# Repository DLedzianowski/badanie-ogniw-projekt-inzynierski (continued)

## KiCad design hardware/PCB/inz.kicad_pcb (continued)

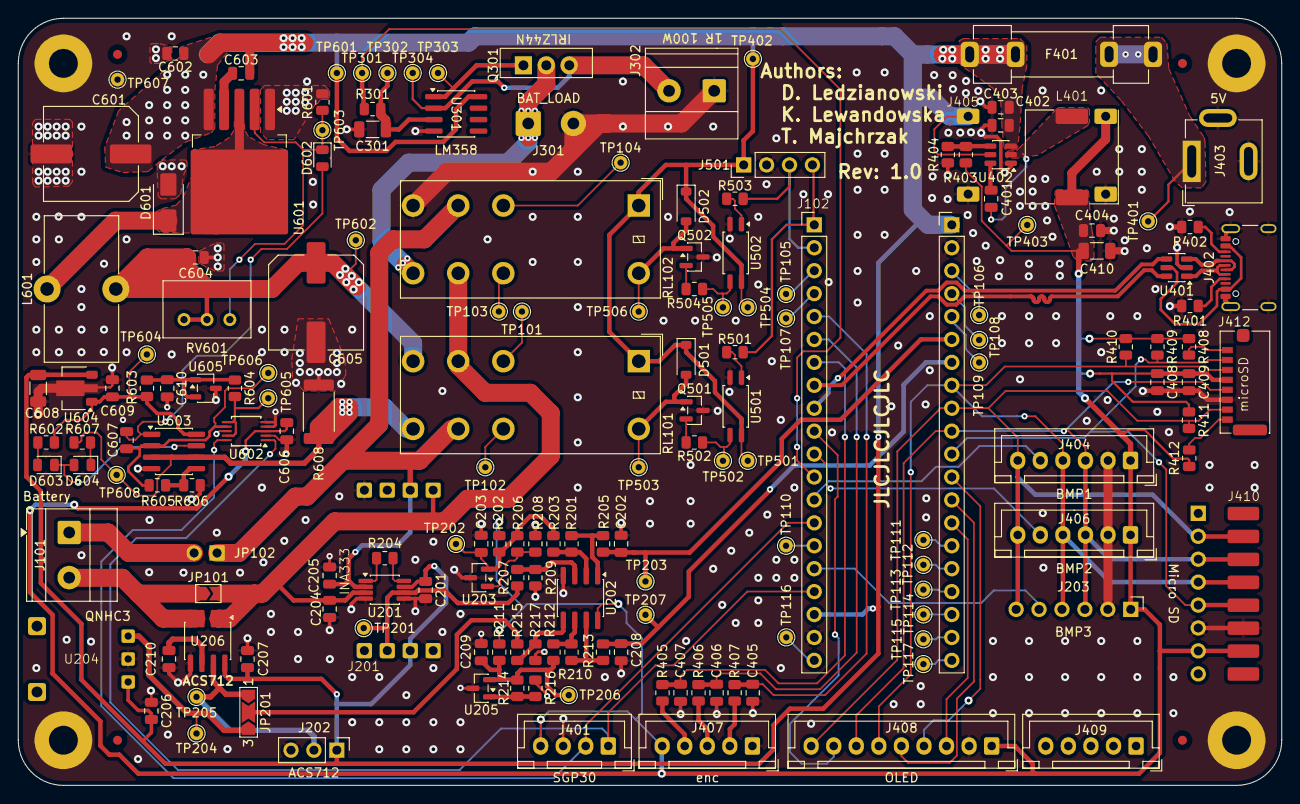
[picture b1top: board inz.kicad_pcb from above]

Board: 2 copper layers, 140.0 x 85.0 mm, 180 parts (0 on the bottom side), 104 nets.

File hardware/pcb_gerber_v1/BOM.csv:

Comment,Designator,Footprint,LCSC part number ,Qty,MFR Part,Manufacturer
100n,"C201,C202,C204,C205,C206,C207,C208,C401,C405,C406,C407,C408",Capacitor_SMD:C_0805_2012Metric,C28233,12," CL21B104KCFNNNE,CL21B104KCFNNNE",Samsung Electro-Mechanics
1u,"C203,C209,C409,C602,C603,C604,C606,C607,C609,C610",Capacitor_SMD:C_0805_2012Metric,C28323,10,CL21B105KBFNNNE,Samsung Electro-Mechanics
1n,C210,Capacitor_SMD:C_0805_2012Metric,C46653,1,CL21B102KBCNNNC,Samsung Electro-Mechanics
10u,"C301,C410,C608",Capacitor_SMD:C_1206_3216Metric,C1849,3,CL31A106KOHNNNE ,Samsung Electro-Mechanics 
2.2u,C402,Capacitor_SMD:C_0805_2012Metric,C377773,1,CL21A225KBQNNNE,Samsung Electro-Mechanics
100n,"C403,C404",Capacitor_SMD:C_0805_2012Metric,C1711,2,CL21B104KBCNNNC,Samsung Electro-Mechanics
470u,"C601,C605",Capacitor_SMD:C_Elec_10x10.2,C3351,2,RVT1E471M1010,Honor Elec
1N4148W,"D501,D502",Diode_SMD:D_SOD-123,C81598,2,1N4148W,ST(Semtech)
MBRD1045,D601,Diode_SMD:D_SMA,C22452,1,C22452,MDD(Microdiode Semiconductor)
Red,D602,LED_SMD:LED_0805_2012Metric,C84256,1,NCD0805R1,Foshan NationStar Optoelectronics
Yellow,D603,LED_SMD:LED_0805_2012Metric,C2296,1,KT-0805Y,Hubei KENTO Elec
Green,D604,LED_SMD:LED_0805_2012Metric,C2297,1,KT-0805G,Hubei KENTO Elec
STM32blackpill,J102,Package_DIP:DIP-40_W15.24mm,C2332,1,ICSockets-40P,BOOMELE(Boom Precision Elec)
"BMP1,BMP2","J404,J406",Connector_JST:JST_XH_B6B-XH-A_1x06_P2.50mm_Vertical,C144397,2,B6B-XH-A(LF)(SN),JST
SGP30,J401,Connector_JST:JST_XH_B4B-XH-A_1x04_P2.50mm_Vertical,C144395,1,B4B-XH-A(LF)(SN),JST
USBC,J402,footprints:USB_C_16P,C47817612,1,TYPE-C-31-M-48,Korean Hroparts Elec
5V,J403,Connector_BarrelJack:BarrelJack_GCT_DCJ200-10-A_Horizontal,C5155559,1,DC-005H-D020,G-Switch
enc,J407,Connector_JST:JST_XH_B5B-XH-A_1x05_P2.50mm_Vertical,C157991,1,B5B-XH-A(LF)(SN),JST
OLED,J408,Connector_JST:JST_XH_B9B-XH-A_1x09_P2.50mm_Vertical,C157966,1,B9B-XH-A(LF)(SN) ,JST
Micro_SD_Card,J412,footprints:microSD,C498185,1,TF-021B-H265,SOFNG
2.2uH,L401,"footprints:SMD,10.4x10.3mm",C10164 ,1,SXN(Shun Xiang Nuo Elec),SMDRH105R-2R2NT 
47u,L601,Inductor_THT:L_Toroid_Vertical_L16.0mm_W8.0mm_P7.62mm,C18213949,1,XR050125TS470MVL8,XR
IRLZ44N,Q301,Package_TO_SOT_THT:TO-220-3_Vertical,C38774,1,IRLZ44NPBF,Infineon Technologies
NPN,"Q501,Q502",Package_TO_SOT_SMD:SOT-23,C20526,2,MMBT3904(RANGE:100-300),"Jiangsu Changjing Electronics Technology Co., Ltd."
6.2k,"R201,R209",Resistor_SMD:R_0805_2012Metric,C17767,2,0805W8F6201T5E,UNI-ROYAL(Uniroyal Elec)
10k,"R202,R206,R208,R211,R216,R408,R409,R410,R411,R412,R606",Resistor_SMD:R_0805_2012Metric,C17414,11,0805W8F1002T5E,UNI-ROYAL(Uniroyal Elec)
3.9k,"R203,R207",Resistor_SMD:R_0805_2012Metric,C17614,2,0805W8F3901T5E,UNI-ROYAL(Uniroyal Elec)
4.7k,"R205,R212,R213,R215",Resistor_SMD:R_0805_2012Metric,C17673,4,0805W8F4701T5E,UNI-ROYAL(Uniroyal Elec)
8.2k,"R210,R217",Resistor_SMD:R_0805_2012Metric,C17828 ,2,0805W8F8201T5E,UNI-ROYAL(Uniroyal Elec)
2.2k,R214,Resistor_SMD:R_0805_2012Metric,C17520 ,1,0805W8F2201T5E,UNI-ROYAL(Uniroyal Elec)
1k,"R301,R602,R607",Resistor_SMD:R_0805_2012Metric,C17513,3,0805W8F1001T5E,UNI-ROYAL(Uniroyal Elec)
5.1k,"R401,R402,R405,R406,R407",Resistor_SMD:R_0805_2012Metric,C27834,5,0805W8F5101T5E ,UNI-ROYAL(Uniroyal Elec)
100k,R403,Resistor_SMD:R_0805_2012Metric,C149504,1,0805W8F1003T5E,UNI-ROYAL(Uniroyal Elec)
22.1k,R404,Resistor_SMD:R_0805_2012Metric,C17552 ,1,0805W8F2212T5E ,UNI-ROYAL(Uniroyal Elec)
220R,"R501,R502,R503,R504",Resistor_SMD:R_0805_2012Metric,C17557,4,0805W8F2200T5E,UNI-ROYAL(Uniroyal Elec)
2.2k,R603,Resistor_SMD:R_0805_2012Metric,C17520,1,0805W8F2201T5E,UNI-ROYAL(Uniroyal Elec)
71.5k,R604,Resistor_SMD:R_0805_2012Metric,C17811,1,0805W8F7152T5E,UNI-ROYAL(Uniroyal Elec)
90.9k,R605,Resistor_SMD:R_0805_2012Metric,C17860,1,0805W8F9092T5E,UNI-ROYAL(Uniroyal Elec)
0.05R,R608,Resistor_SMD:R_2512_6332Metric,C127698,1,25121WF500MT4E,UNI-ROYAL(Uniroyal Elec)
INA333xxDGK,U201,Package_SO:VSSOP-8_3x3mm_P0.65mm,C2057648,1, INA333AIDGKT,Texas Instruments
MCP6002T-I/SN,U202,Package_SO:SOIC-8_3.9x4.9mm_P1.27mm,C7377,1, MCP6002T-I/SN,Microchip Tech
TLV431,"U203,U205",Package_TO_SOT_SMD:SOT-23,C56765,2,TLV431AIDBZR,Texas Instruments
ACS712xLCTR-05B,U206,Package_SO:SOIC-8_3.9x4.9mm_P1.27mm,C44471,1,ACS712ELCTR-05B-T,"Allegro MicroSystems, LLC"
LM358,"U301,U603",Package_SO:SOIC-8_3.9x4.9mm_P1.27mm,C7950 ,2,LM358DR2G,onsemi 
USBLC6-2SC6,U401,Package_TO_SOT_SMD:SOT-23-6,C7519,1,USBLC6-2SC6,STMicroelectronics
LMR51430,U402,Package_TO_SOT_SMD:SOT-23-6,C5185863,1,LMR51430XDDCR,Texas Instruments
LTV-217,"U501,U502",Package_SO:SOP-4_4.4x2.6mm_P1.27mm,C115450,2,LTV-217-B-G,Lite-On
XL4015,U601,Package_TO_SOT_SMD:TO-263-5_TabPin3,C51661,1,XL4015E1,XLSEMI
DS3502U+T&R,U602,Package_SO:TSSOP-10_3x3mm_P0.5mm,C2649363,1,DS3502U+T&R ,Analog Devices Inc./Maxim Integrated
78L05,U604,Package_TO_SOT_SMD:SOT-89-3,C71136,1,78L05G-AB3-R,UTC(Unisonic Tech)
TL431,U605,Package_TO_SOT_SMD:SOT-23-3,C190245,1,TL431BQDBZR,Texas Instruments
270,R601,Resistor_SMD:R_0805_2012Metric,Resistor_SMD:R_0805_2012Metric,1,0805W8F2700T5E,UNI-ROYAL(Uniroyal Elec)

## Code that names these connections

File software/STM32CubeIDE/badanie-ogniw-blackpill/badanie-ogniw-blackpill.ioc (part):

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Mcu.Name=STM32F411C(C-E)Ux
Mcu.Package=UFQFPN48
Mcu.UserName=STM32F411CEUx
PA0-WKUP.Signal=ADCx_IN0
PA1.GPIOParameters=PinState,GPIO_PuPd,GPIO_Label
PA1.GPIO_Label=oled_CS
PA1.GPIO_PuPd=GPIO_PULLUP
PA1.PinState=GPIO_PIN_SET
PA1.Signal=GPIO_Output
PA10.GPIOParameters=GPIO_PuPd,GPIO_Label,GPIO_ModeDefaultEXTI
PA10.GPIO_Label=enc_KEY
PA10.GPIO_ModeDefaultEXTI=GPIO_MODE_IT_FALLING
PA10.GPIO_PuPd=GPIO_PULLUP
PA10.Signal=GPXTI10
PA11.Mode=Device_Only
PA11.Signal=USB_OTG_FS_DM
PA12.Mode=Device_Only
PA12.Signal=USB_OTG_FS_DP
PA13.Mode=Serial_Wire
PA13.Signal=SYS_JTMS-SWDIO
PA14.Mode=Serial_Wire
PA14.Signal=SYS_JTCK-SWCLK
PA15.GPIOParameters=GPIO_Label
PA15.GPIO_Label=PWM
PA15.Signal=S_TIM2_CH1_ETR
PA2.GPIOParameters=GPIO_Label
PA2.GPIO_Label=oled_RST
PA2.Signal=GPIO_Output
PA3.GPIOParameters=GPIO_Label
PA3.GPIO_Label=oled_DC
PA3.Signal=GPIO_Output
PA4.GPIOParameters=GPIO_Speed,PinState,GPIO_PuPd,GPIO_Label
PA4.GPIO_Label=sd_CS
PA4.GPIO_PuPd=GPIO_PULLUP
PA4.GPIO_Speed=GPIO_SPEED_FREQ_HIGH
PA4.PinState=GPIO_PIN_SET
PA4.Signal=GPIO_Output
PA5.Mode=Full_Duplex_Master
PA5.Signal=SPI1_SCK
PA6.Mode=Full_Duplex_Master
PA6.Signal=SPI1_MISO
PA7.Mode=Full_Duplex_Master
PA7.Signal=SPI1_MOSI
PA8.GPIOParameters=GPIO_Label
PA8.GPIO_Label=enc_CH1
PA8.Signal=S_TIM1_CH1
PA9.GPIOParameters=GPIO_Label
PA9.GPIO_Label=enc_CH2
PA9.Signal=S_TIM1_CH2
PB0.Signal=ADCx_IN8
PB1.Signal=ADCx_IN9
PB12.GPIOParameters=PinState,GPIO_PuPd,GPIO_Label
PB12.GPIO_Label=R1IN1
PB12.GPIO_PuPd=GPIO_PULLDOWN
PB12.PinState=GPIO_PIN_RESET
PB12.Signal=GPIO_Output
PB13.GPIOParameters=PinState,GPIO_PuPd,GPIO_Label
PB13.GPIO_Label=R1IN2
PB13.GPIO_PuPd=GPIO_PULLDOWN
PB13.PinState=GPIO_PIN_RESET
PB13.Signal=GPIO_Output
PB14.GPIOParameters=GPIO_PuPd,GPIO_Label
PB14.GPIO_Label=lipol_detection
PB14.GPIO_PuPd=GPIO_PULLUP
PB14.Signal=GPXTI14
PB15.GPIOParameters=GPIO_PuPd,GPIO_Label
PB15.GPIO_Label=liion_detection
PB15.GPIO_PuPd=GPIO_PULLUP
PB15.Signal=GPXTI15
PB3.GPIOParameters=PinState,GPIO_PuPd,GPIO_Label
PB3.GPIO_Label=bmp2_CS
PB3.GPIO_PuPd=GPIO_PULLUP
PB3.PinState=GPIO_PIN_SET
PB3.Signal=GPIO_Output
PB4.GPIOParameters=GPIO_Label
PB4.GPIO_Label=PWM_discharge
PB4.Signal=S_TIM3_CH1
PB5.GPIOParameters=PinState,GPIO_PuPd,GPIO_Label
PB5.GPIO_Label=bmp1_CS
PB5.GPIO_PuPd=GPIO_PULLUP
PB5.PinState=GPIO_PIN_SET
PB5.Signal=GPIO_Output
PB6.Mode=I2C
PB6.Signal=I2C1_SCL
PB7.GPIOParameters=GPIO_Label
PB7.GPIO_Label=PWM_charge
PB7.Signal=S_TIM4_CH2
PB8.GPIOParameters=PinState,GPIO_PuPd,GPIO_Label
PB8.GPIO_Label=bmp3_CS
PB8.GPIO_PuPd=GPIO_PULLUP
PB8.PinState=GPIO_PIN_SET
PB8.Signal=GPIO_Output
PB9.Mode=I2C
PB9.Signal=I2C1_SDA
PC13-ANTI_TAMP.GPIOParameters=PinState,GPIO_PuPd,GPIO_Label
PC13-ANTI_TAMP.GPIO_Label=LED
PC13-ANTI_TAMP.GPIO_PuPd=GPIO_NOPULL
PC13-ANTI_TAMP.PinState=GPIO_PIN_SET
PC13-ANTI_TAMP.Signal=GPIO_Output
PH0\ -\ OSC_IN.Mode=HSE-External-Oscillator
PH0\ -\ OSC_IN.Signal=RCC_OSC_IN
PH1\ -\ OSC_OUT.Mode=HSE-External-Oscillator
PH1\ -\ OSC_OUT.Signal=RCC_OSC_OUT
RCC.HSE_VALUE=25000000
RCC.SYSCLKFreq_VALUE=72000000
RCC.SYSCLKSource=RCC_SYSCLKSOURCE_PLLCLK
board=custom

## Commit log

2025-04-06 Initial commit
    SPI: BMP280, OLED, czytnik SD
2025-04-08 SD csv file
2025-04-12 SGP, INA219
2025-08-18 stm32 blackpill
2025-08-22 OLED GUI
2025-09-16 Automate measurement cycle
2025-09-28 batery ADC, OLED
2025-09-30 sd, macro
2025-10-12 OLED
2025-10-13 SD FIX
2025-11-06 acs712
2025-11-10 ina333, ACS712
2025-11-20 test com
2025-11-22 pcb commit
2025-11-26 pcb sensors
2025-11-30 Rough Layout pcb
2025-12-03 pcb XL4015
2025-12-04 XL4015 CC, relays
2025-12-07 pcb relay
2025-12-07 PCB routing
2025-12-07 PCB final routing
2025-12-08 PCB final design
2026-01-04 oled1.8
2026-01-09 OLED 2.8, BME, SGP calibration, enc
2026-01-12 oled, sd
2026-01-13 control_battery_state
2026-01-13 OLED_manage
2026-01-18 usb, sd
2026-01-19 sgpAH, relay
